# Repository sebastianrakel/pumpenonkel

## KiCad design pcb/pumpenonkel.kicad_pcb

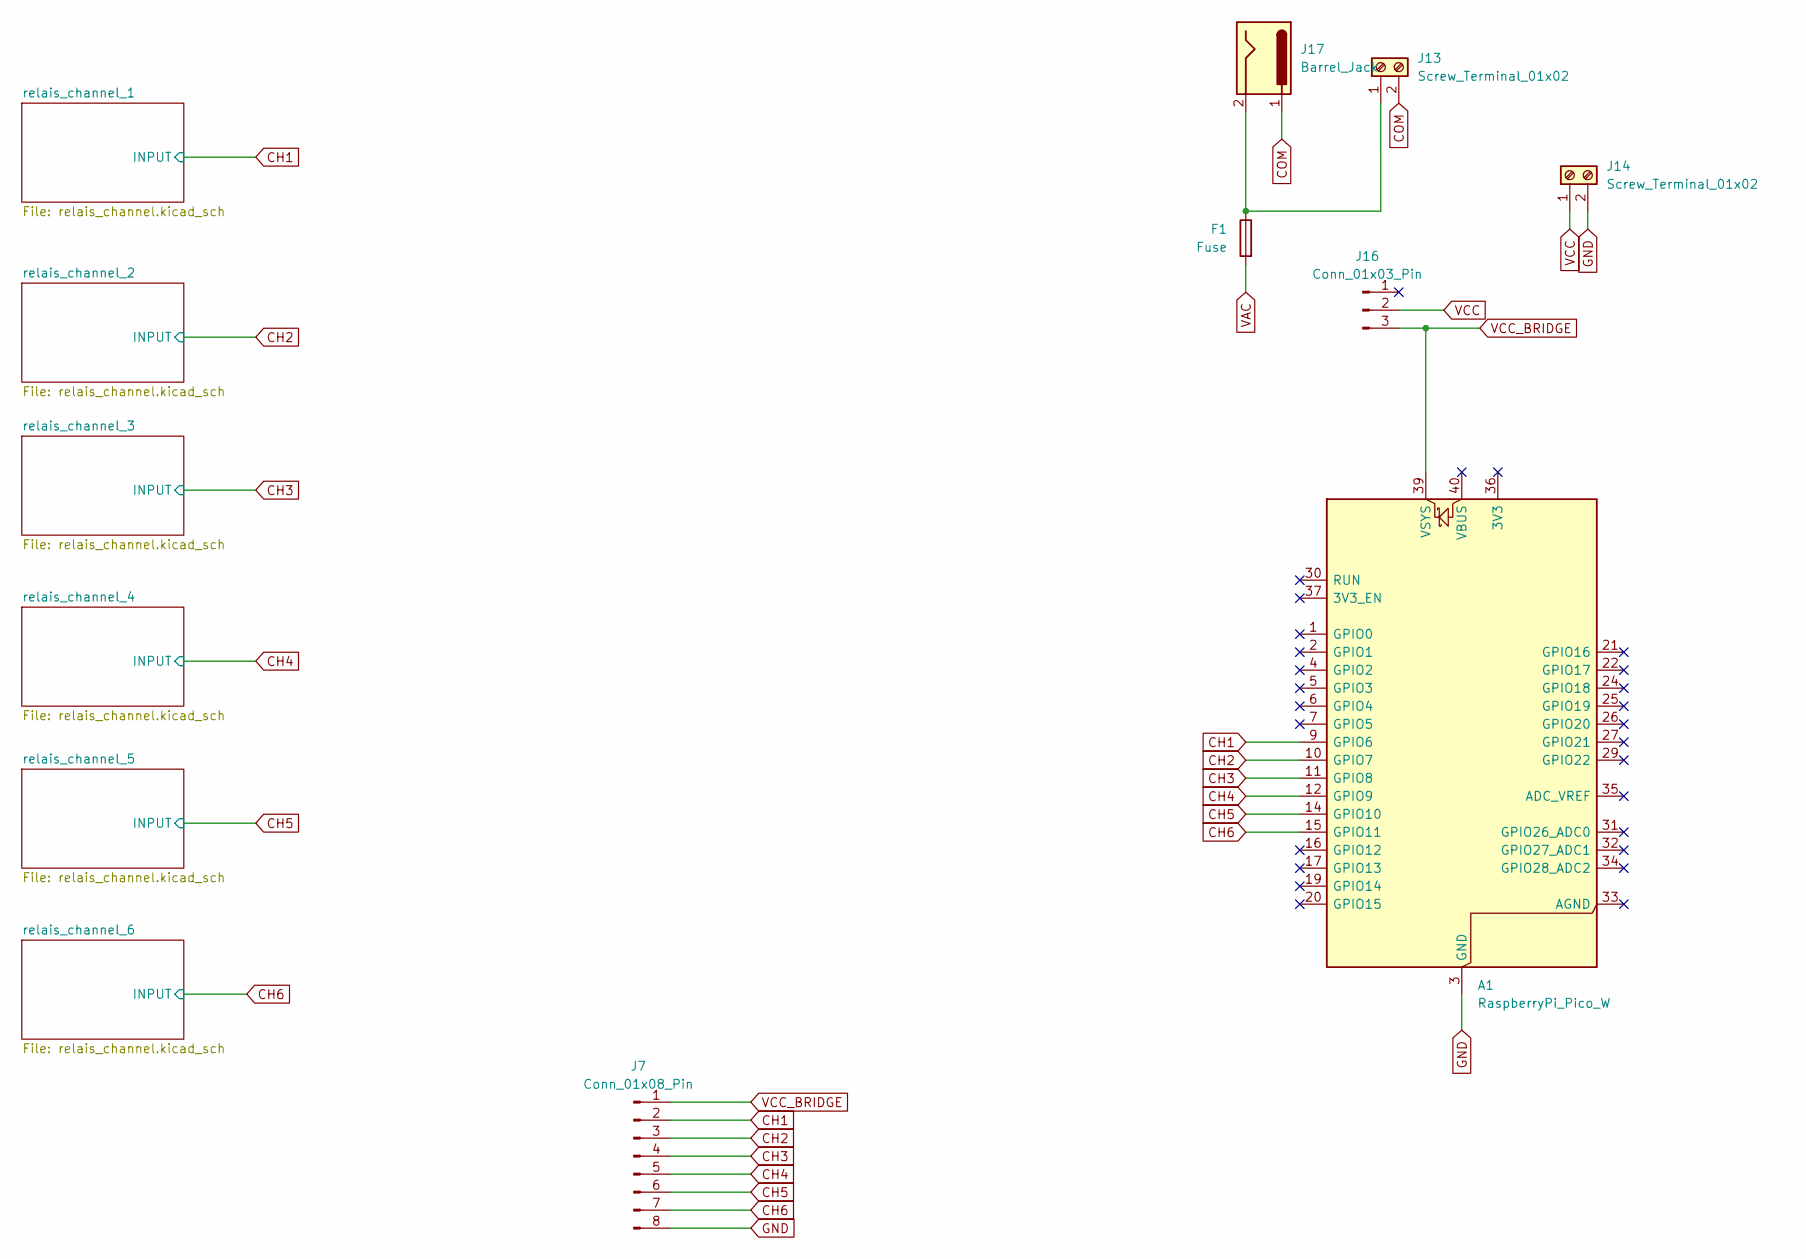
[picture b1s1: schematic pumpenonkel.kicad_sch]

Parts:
A1: RaspberryPi_Pico_W; RaspberryPi_Pico_Common_THT
F1: Fuse; Fuseholder_Clip-5x20mm_Littelfuse_111_Lateral_P18.80x5.00mm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
J7: Conn_01x08_Pin; PinHeader_1x08_P2.54mm_Vertical
J13, J14: Screw_Terminal_01x02; TerminalBlock_MaiXu_MX126-5.0-02P_1x02_P5.00mm
J16: Conn_01x03_Pin; PinHeader_1x03_P2.54mm_Vertical
J17: Barrel_Jack; BarrelJack_CUI_PJ-063AH_Horizontal

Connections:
CH1: A1.9 (GPIO6), J7.2; also elsewhere on the board
CH2: A1.10 (GPIO7), J7.3; also elsewhere on the board
CH3: A1.11 (GPIO8), J7.4; also elsewhere on the board
CH4: A1.12 (GPIO9), J7.5; also elsewhere on the board
CH5: A1.14 (GPIO10), J7.6; also elsewhere on the board
CH6: A1.15 (GPIO11), J7.7; also elsewhere on the board
COM: J13.2, J17.1; also elsewhere on the board
GND: A1.3 (GND), A1.8 (GND), A1.13 (GND), A1.18 (GND), A1.23 (GND), A1.28 (GND), A1.38 (GND), J7.8, J14.2; also elsewhere on the board
unnamed: F1.1, J13.1, J17.2
VAC: F1.2; also elsewhere on the board
VCC: J14.1, J16.2; also elsewhere on the board
VCC_BRIDGE: A1.39 (VSYS), J7.1, J16.3

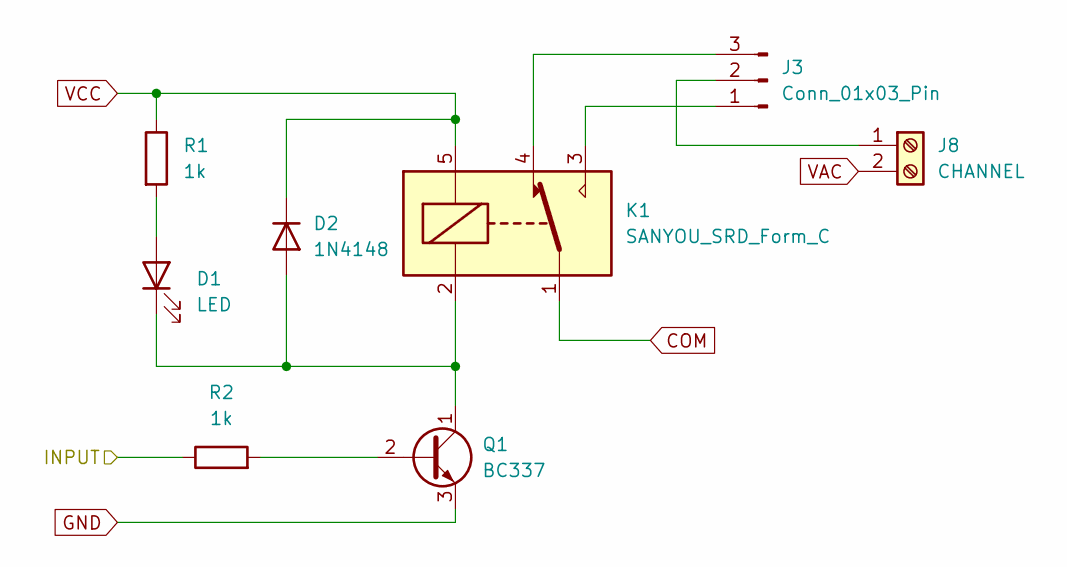
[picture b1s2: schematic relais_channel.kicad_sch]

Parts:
D1: LED; LED_D3.0mm
D2: 1N4148; D_DO-35_SOD27_P7.62mm_Horizontal
J3: Conn_01x03_Pin; PinHeader_1x03_P2.54mm_Vertical
J8: CHANNEL; TerminalBlock_MaiXu_MX126-5.0-02P_1x02_P5.00mm
K1: SANYOU_SRD_Form_C; Relay_SPDT_SANYOU_SRD_Series_Form_C
Q1: BC337; TO-92
R1, R2: 1k; R_Axial_DIN0207_L6.3mm_D2.5mm_P7.62mm_Horizontal

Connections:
CH1: R2.1; also elsewhere on the board
COM: K1.1; also elsewhere on the board
GND: Q1.3 (E); also elsewhere on the board
unnamed: D1.2 (A), R1.2
unnamed: D1.1 (K), D2.2 (A), K1.2, Q1.1 (C)
unnamed: J3.1, K1.3
unnamed: J3.2, J8.1
unnamed: J3.3, K1.4
unnamed: Q1.2 (B), R2.2
VAC: J8.2; also elsewhere on the board
VCC: D2.1 (K), K1.5, R1.1; also elsewhere on the board

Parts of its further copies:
D3, D5, D7, D9, D11: LED; LED_D3.0mm
D4, D6, D8, D10, D12: 1N4148; D_DO-35_SOD27_P7.62mm_Horizontal
J1, J2, J4, J5, J6: Conn_01x03_Pin; PinHeader_1x03_P2.54mm_Vertical
J9, J10, J11, J12, J15: CHANNEL; TerminalBlock_MaiXu_MX126-5.0-02P_1x02_P5.00mm
K2, K3, K4, K5, K6: SANYOU_SRD_Form_C; Relay_SPDT_SANYOU_SRD_Series_Form_C
Q2, Q3, Q4, Q5, Q6: BC337; TO-92
R3, R4, R5, R6, R7, R8, R9, R10, R11, R12: 1k; R_Axial_DIN0207_L6.3mm_D2.5mm_P7.62mm_Horizontal

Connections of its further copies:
CH2: R4.1; also elsewhere on the board
CH3: R6.1; also elsewhere on the board
CH4: R8.1; also elsewhere on the board
CH5: R10.1; also elsewhere on the board
CH6: R12.1; also elsewhere on the board
COM: K2.1, K3.1, K4.1, K5.1, K6.1; also elsewhere on the board
GND: Q2.3 (E), Q3.3 (E), Q4.3 (E), Q5.3 (E), Q6.3 (E); also elsewhere on the board
unnamed: D3.2 (A), R3.2
unnamed: D3.1 (K), D4.2 (A), K2.2, Q2.1 (C)
unnamed: D5.2 (A), R5.2
unnamed: D5.1 (K), D6.2 (A), K3.2, Q3.1 (C)
unnamed: D7.2 (A), R7.2
unnamed: D7.1 (K), D8.2 (A), K4.2, Q4.1 (C)
unnamed: D9.2 (A), R9.2
unnamed: D9.1 (K), D10.2 (A), K5.2, Q5.1 (C)
unnamed: D11.2 (A), R11.2
unnamed: D11.1 (K), D12.2 (A), K6.2, Q6.1 (C)
unnamed: J1.1, K2.3
unnamed: J1.2, J9.1
unnamed: J1.3, K2.4
unnamed: J2.1, K3.3
unnamed: J2.3, K3.4
unnamed: J4.1, K4.3
unnamed: J4.3, K4.4
unnamed: J5.1, K5.3
unnamed: J5.3, K5.4
unnamed: J6.1, K6.3
unnamed: J6.3, K6.4
unnamed: J2.2, J10.1
unnamed: J4.2, J11.1
unnamed: J5.2, J12.1
unnamed: J6.2, J15.1
unnamed: Q2.2 (B), R4.2
unnamed: Q3.2 (B), R6.2
unnamed: Q4.2 (B), R8.2
unnamed: Q5.2 (B), R10.2
unnamed: Q6.2 (B), R12.2
VAC: J9.2, J10.2, J11.2, J12.2, J15.2; also elsewhere on the board
VCC: D4.1 (K), D6.1 (K), D8.1 (K), D10.1 (K), D12.1 (K), K2.5, K3.5, K4.5, K5.5, K6.5, R3.1, R5.1, R7.1, R9.1, R11.1; also elsewhere on the board

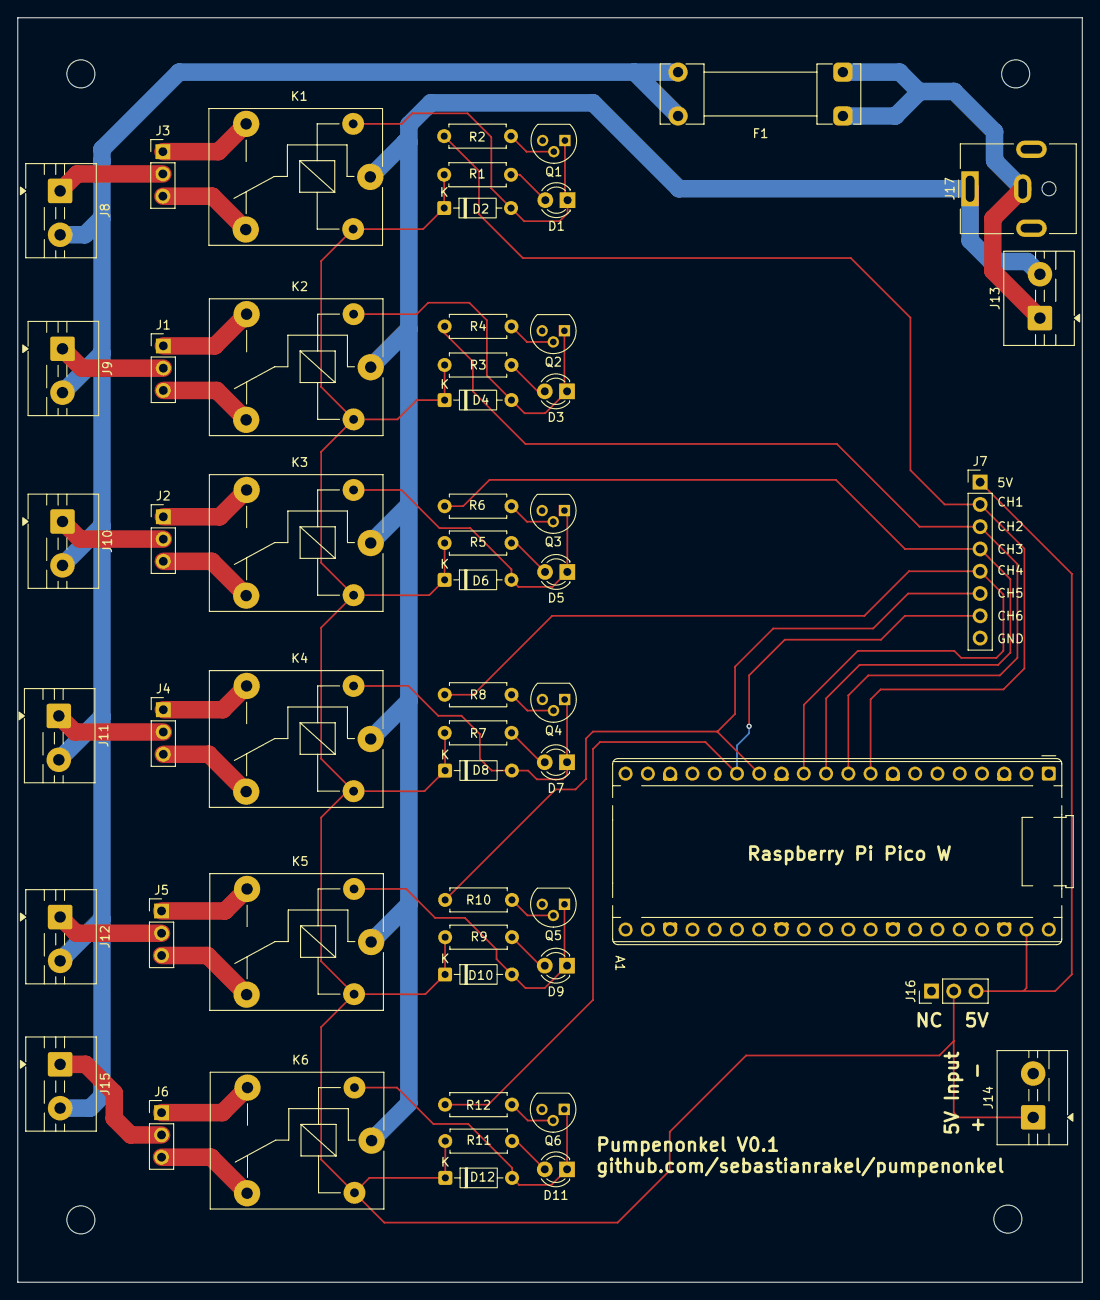
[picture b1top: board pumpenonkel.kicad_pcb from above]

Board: 2 copper layers, 121.4 x 144.2 mm, 55 parts (0 on the bottom side), 48 nets.

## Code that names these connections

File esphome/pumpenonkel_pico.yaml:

esphome:
  name: pumpenonkel_pico

rp2040:
  board: rpipicow
  framework:
    platform_version: https://github.com/maxgerhardt/platform-raspberrypi.git

# Enable logging
logger:

web_server:
  port: 80
# Enable Home Assistant API
api:

ota:
  - platform: esphome
    password: ""

captive_portal:

wifi:
  ssid: !secret wifi_name
  password: !secret wifi_password

  # Enable fallback hotspot (captive portal) in case wifi connection fails
  ap:
    ssid: "Pumpenonkel Fallback Hotspot"
    password: "XTWMRkP72S7d"
    
switch:
  - platform: gpio
    pin: GPIO11
    name: "Kanal 6"
    id: kanal_6
  - platform: gpio
    pin: GPIO10
    name: "Kanal 5"
    id: kanal_5
  - platform: gpio
    pin: GPIO9
    name: "Kanal 4"
    id: kanal_4
  - platform: gpio
    pin: GPIO8
    name: "Kanal 3"
    id: kanal_3
  - platform: gpio
    pin: GPIO7
    name: "Kanal 2"
    id: kanal_2
  - platform: gpio
    pin: GPIO6
    name: "Kanal 1"
    id: kanal_1
  

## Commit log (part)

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2026-05-05 Update PCB
2026-05-27 finalilise pcb
2026-06-01 Add bom
